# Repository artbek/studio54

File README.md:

Infinity mirror necklace (Fancy dress prop)
===========================================

Video: https://youtu.be/G1R_iDx5s8U

<br />

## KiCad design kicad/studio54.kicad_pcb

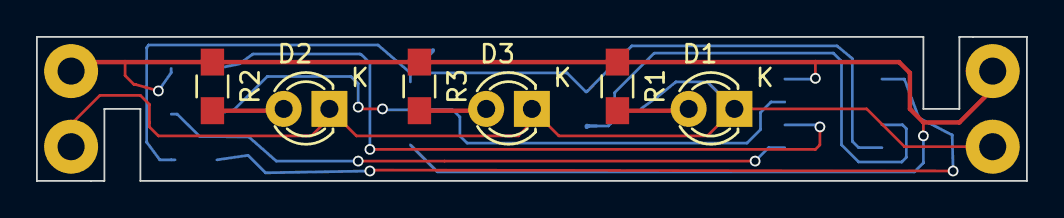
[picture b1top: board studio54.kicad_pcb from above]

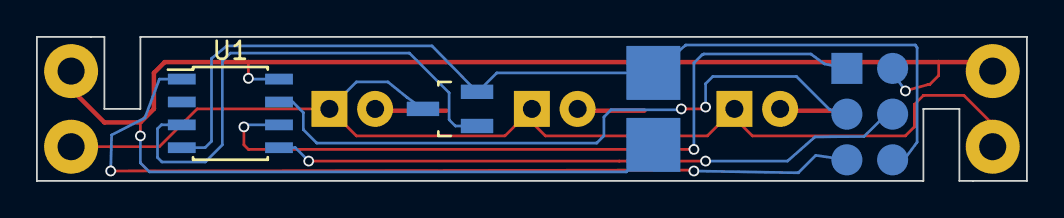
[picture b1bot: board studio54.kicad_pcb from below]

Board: 2 copper layers, 55.0 x 8.0 mm, 15 parts (5 on the bottom side), 11 nets.

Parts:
D1, D2, D3: LED; LED-3MM
J1, J3, J6, J8: CONN_01X01; Measurement_Point_Round-TH_Big-no_silk
J4: CONN_02X03; SMD_Pin_Header_2x3
J10_SMD1, J11_SMD1: CONN_01X01; Measurement_Point_Square-SMD-Pad_Big-no_silk
Q1: BSS138; SOT-23_Handsoldering-no_silk
R1, R2, R3: R; R_0805_HandSoldering
U1: ATTINY13-20SSU; SOIC-8_3.9x4.9mm_Pitch1.27mm

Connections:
GND: J4.6, J11_SMD1.1, Q1.2, U1.4
unnamed: D1.1, D2.1, D3.1, J1.1, J3.1, Q1.3
unnamed: D1.2, R1.2
unnamed: D2.2, R2.2
unnamed: D3.2, R3.2
unnamed: J4.1, U1.6
unnamed: J4.3, U1.7
unnamed: J4.4, U1.5
unnamed: J4.5, U1.1
unnamed: Q1.1, U1.3
VDD: J4.2, J6.1, J8.1, J10_SMD1.1, R1.1, R2.1, R3.1, U1.8

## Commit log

2017-04-30 Initial.
2020-03-04 [README]: description + images + tidy-up.
2020-03-04 [README]: fix broken links.
